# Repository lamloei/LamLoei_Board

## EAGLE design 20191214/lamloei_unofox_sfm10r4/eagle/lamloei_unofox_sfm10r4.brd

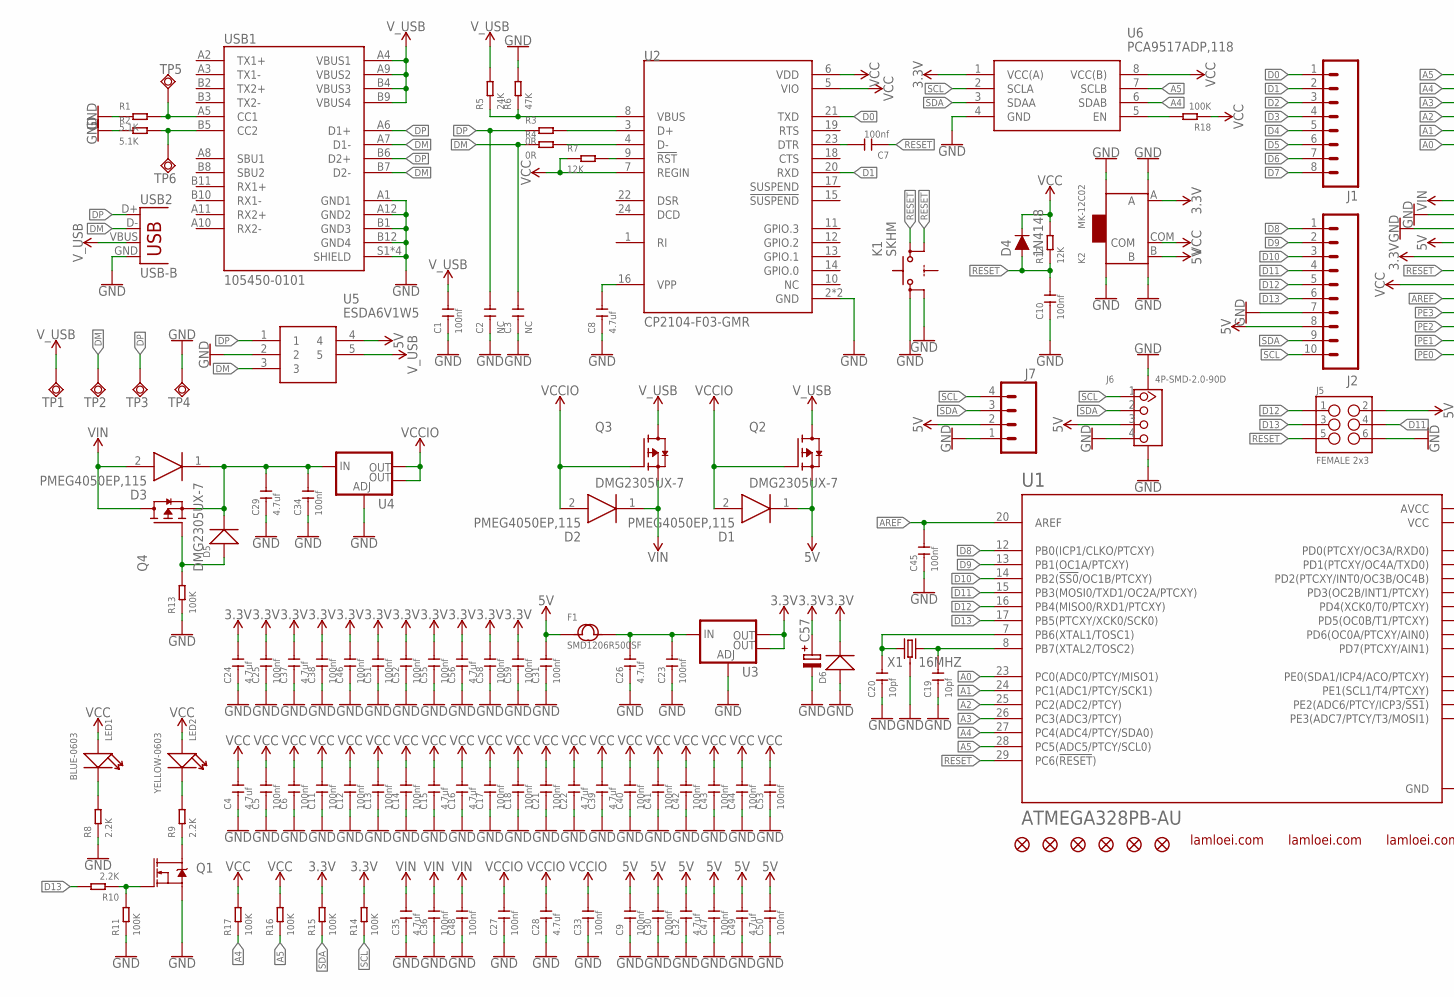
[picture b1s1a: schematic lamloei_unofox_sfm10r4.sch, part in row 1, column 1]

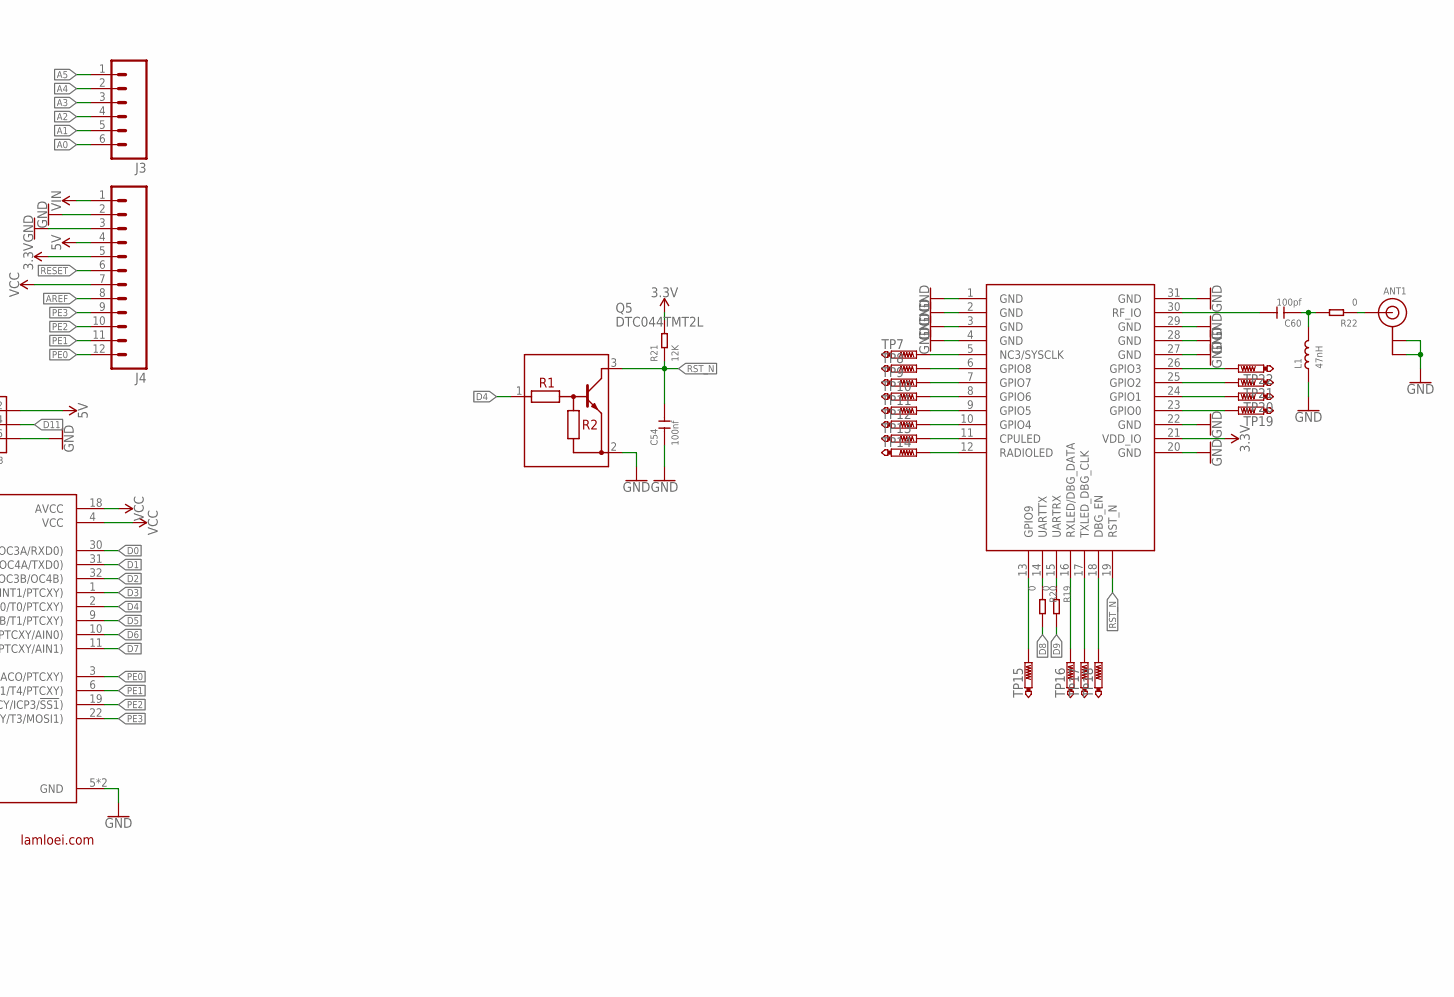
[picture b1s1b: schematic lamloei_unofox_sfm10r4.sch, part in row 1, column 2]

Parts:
ANT1: ANTENNA_U.FL; U.FL
C1, C5, C6, C7, C9, C10, C11, C12, C13, C14, C17, C18, C21, C23, C25, C27, C30, C31, C33, C34, C36, C38, C40, C41, C42, C43, C44, C45, C46, C47, C48, C50, C51, C52, C53, C54, C55, C58, C59: 100nf; C0402
C2, C3: NC; C0402
C4, C8, C15, C16, C22, C24, C26, C28, C29, C32, C35, C37, C39, C49, C56: 4.7uf; C0805
C19, C20: 10pf; C0402
C57: C-PR-SMD-TE-D; TE-D-7343
C60: 100pf; C0402
D1, D2, D3: PMEG4050EP,115; SODFL4725X110N
D4: 1N4148; SOD-323
D5, D6: DIODE'1N4148-SMD'; LL-34
F1: SMD1206R500SF; F1206
J1: M08SILK_FEMALE_PTH; 1X08
J2: M10SILK_FEMALE_PTH; 1X10
J3: M06SILK_FEMALE_PTH; 1X06
J4: M12PTH; 1X12
J5: FEMALE 2x3; 2X3
J6: 4P-SMD-2.0-90D; HW4-SMD-2.0-90D
J7: M04LONGPADS; 1X04_LONGPADS
K1: SKHM
K2: MK-12C02; SW7-SMD-L6.7X2.7X3.2MM
L1: 47nH; L0603
LED1: BLUE-0603; LED-0603
LED2: YELLOW-0603; LED-0603
Q1: 220mA/50V/3.5Ω; SOT23-3
Q2, Q3, Q4: DMG2305UX-7; SOT91P240X110-3N_DMG2305UX-7
Q5: DTC044TMT2L; SOTFL40P120X55-3N
R1, R2: 5.1K; R0402
R3, R4: 0R; R0402
R5: 24K; R0402
R6: 47K; R0402
R7, R12, R21: 12K; R0402
R8, R9, R10: 2.2K; R0402
R11, R13, R14, R15, R16, R17, R18: 100K; R0402
R19, R20, R22: 0; R0402
TP1, TP2, TP3, TP4, TP5, TP6: TPSQTP13SQ; TP13SQ
TP7, TP8, TP9, TP10, TP11, TP12, TP13, TP14, TP15, TP16, TP17, TP18, TP19, TP20, TP21, TP22: PTR1B1,27; B1,27
U1: ATMEGA328PB-AU; QFP80P900X900X120-32N
U2: CP2104-F03-GMR
U3, U4: V_REG_LM1117SOT223; SOT223
U5: ESDA6V1W5; SOT65P210X110-5N
U6: PCA9517ADP,118; SOP65P490X110-8N
U7: WSSFM10RWSSFM10R2R4; WSSFM10R
USB1: 105450-0101
USB2: USB-B; USB-B-PTH
X1: 16MHZ; CRYSTAL-SMD-3.2X2.5MM
ZFC1, ZFC2, ZFC3: FIDUCIAL1X2; FIDUCIAL-1X2
ZFD1, ZFD2, ZFD3: FIDUCIAL1X2; FIDUCIAL-1X2
ZL1, ZL2: LAMLEOI_LOGO_3
ZL3: LAMLOEI_BIGLOGO

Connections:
3.3V: C24.2, C25.2, C37.2, C38.2, C46.2, C51.2, C52.2, C55.2, C56.2, C57.+, C58.2, C59.2, D6.C (-), J4.5, K2.A, R14.2, R15.2, R21.2, U3.2 (OUT), U3.4 (OUT), U6.1 (VCC(A)), U7.21 (VDD_IO)
5V: C9.2, C30.2, C31.2, C32.2, C47.2, C49.2, C50.2, D1.1 (K), F1.1, J2.8, J4.4, J5.2, J6.3, J7.2, K2.B, Q2.2 (S), U5.4
A0: J3.6, U1.23 (PC0(ADC0/PTCY/MISO1))
A1: J3.5, U1.24 (PC1(ADC1/PTCY/SCK1))
A2: J3.4, U1.25 (PC2(ADC2/PTCY))
A3: J3.3, U1.26 (PC3(ADC3/PTCY))
A4: J3.2, R17.1, U1.27 (PC4(ADC4/PTCY/SDA0)), U6.6 (SDAB)
A5: J3.1, R16.1, U1.28 (PC5(ADC5/PTCY/SCL0)), U6.7 (SCLB)
AREF: C45.2, J4.8, U1.20 (AREF)
D0: J1.1, U1.30 (PD0(PTCXY/OC3A/RXD0)), U2.21 (TXD)
D1: J1.2, U1.31 (PD1(PTCXY/OC4A/TXD0)), U2.20 (RXD)
D2: J1.3, U1.32 (PD2(PTCXY/INT0/OC3B/OC4B))
D3: J1.4, U1.1 (PD3(OC2B/INT1/PTCXY))
D4: J1.5, Q5.1 (B), U1.2 (PD4(XCK0/T0/PTCXY))
D5: J1.6, U1.9 (PD5(OC0B/T1/PTCXY))
D6: J1.7, U1.10 (PD6(OC0A/PTCXY/AIN0))
D7: J1.8, U1.11 (PD7(PTCXY/AIN1))
D8: J2.1, R20.2, U1.12 (PB0(ICP1/CLKO/PTCXY))
D9: J2.2, R19.2, U1.13 (PB1(OC1A/PTCXY))
D10: J2.3, U1.14 (PB2(!SS0!/OC1B/PTCXY))
D11: J2.4, J5.4, U1.15 (PB3(MOSI0/TXD1/OC2A/PTCXY))
D12: J2.5, J5.1, U1.16 (PB4(MISO0/RXD1/PTCXY))
D13: J2.6, J5.3, R10.2, U1.17 (PB5(PTCXY/XCK0/SCK0))
DM: C3.2, R4.1, TP2.TP, U5.3, USB1.A7 (D1-), USB1.B7 (D2-), USB2.D-
DP: C2.2, R3.1, TP3.TP, U5.1, USB1.A6 (D1+), USB1.B6 (D2+), USB2.D+
GND: ANT1.1 (GND), ANT1.2 (GND), C1.1, C2.1, C3.1, C4.1, C5.1, C6.1, C8.1, C9.1, C10.1, C11.1, C12.1, C13.1, C14.1, C15.1, C16.1, C17.1, C18.1, C19.1, C20.1, C21.1, C22.1, C23.1, C24.1, C25.1, C26.1, C27.1, C28.1, C29.1, C30.1, C31.1, C32.1, C33.1, C34.1, C35.1, C36.1, C37.1, C38.1, C39.1, C40.1, C41.1, C42.1, C43.1, C44.1, C45.1, C46.1, C47.1, C48.1, C49.1, C50.1, C51.1, C52.1, C53.1, C54.1, C55.1, C56.1, C57.-, C58.1, C59.1, D6.A (+), J2.7, J4.2, J4.3, J5.6, J6.4, J6.SS1, J6.SS2, J7.1, K1.1, K1.2, K2.SS1, K2.SS2, K2.SS3, K2.SS4, L1.1, Q1.2 (S), Q5.2 (E), R1.1, R2.1, R6.2, R8.1, R11.1, R13.1, TP4.TP, U1.5 (GND), U1.21 (GND), U2.2 (GND), U2.25 (GND), U3.1 (ADJ), U4.1 (ADJ), U5.2, U6.4 (GND), U7.1 (GND), U7.2 (GND), U7.3 (GND), U7.4 (GND), U7.20 (GND), U7.22 (GND), U7.27 (GND), U7.28 (GND), U7.29 (GND), U7.31 (GND), USB1.A1 (GND1), USB1.A12 (GND2), USB1.B1 (GND3), USB1.B12 (GND4), USB1.S1 (SHIELD), USB1.S2 (SHIELD), USB1.S3 (SHIELD), USB1.S4 (SHIELD), USB2.GND, X1.2 (3), X1.4 (3)
unnamed: R2.2, TP6.TP, USB1.B5 (CC2)
unnamed: R1.2, TP5.TP, USB1.A5 (CC1)
unnamed: R3.2, U2.3 (D+)
unnamed: R4.2, U2.4 (D-)
unnamed: R5.1, R6.1, U2.8 (VBUS)
unnamed: C23.2, C26.2, F1.2, U3.3 (IN)
unnamed: LED1.-, R8.2
unnamed: C20.2, U1.7 (PB6(XTAL1/TOSC1)), X1.1
unnamed: C7.2, U2.23 (DTR)
unnamed: C29.2, C34.2, D3.1 (K), D5.C (-), Q4.2 (S), U4.3 (IN)
unnamed: R7.2, U2.9 (!RST)
unnamed: LED2.-, R9.2
unnamed: C8.2, U2.16 (VPP)
unnamed: C60.2, U7.30 (RF_IO)
unnamed: C19.2, U1.8 (PB7(XTAL2/TOSC2)), X1.3 (2)
unnamed: R18.2, U6.5 (EN)
unnamed: C60.1, L1.2, R22.2
unnamed: Q1.1 (G), R10.1, R11.2
unnamed: Q1.3 (D), R9.1
unnamed: ANT1.3 (SIGNAL), R22.1
unnamed: R20.1, U7.14 (UARTTX)
unnamed: R19.1, U7.15 (UARTRX)
unnamed: D5.A (+), Q4.1 (G), R13.2
unnamed: TP7.TP, U7.5 (NC3/SYSCLK)
unnamed: TP8.TP, U7.6 (GPIO8)
unnamed: TP9.TP, U7.7 (GPIO7)
unnamed: TP10.TP, U7.8 (GPIO6)
unnamed: TP11.TP, U7.9 (GPIO5)
unnamed: TP12.TP, U7.10 (GPIO4)
unnamed: TP13.TP, U7.11 (CPULED)
unnamed: TP14.TP, U7.12 (RADIOLED)
unnamed: TP22.TP, U7.26 (GPIO3)
unnamed: TP21.TP, U7.25 (GPIO2)
unnamed: TP20.TP, U7.24 (GPIO1)
unnamed: TP19.TP, U7.23 (GPIO0)
unnamed: TP15.TP, U7.13 (GPIO9)
unnamed: TP18.TP, U7.18 (DBG_EN)
unnamed: TP17.TP, U7.17 (TXLED_DBG_CLK)
unnamed: TP16.TP, U7.16 (RXLED/DBG_DATA)
PE0: J4.12, U1.3 (PE0(SDA1/ICP4/ACO/PTCXY))
PE1: J4.11, U1.6 (PE1(SCL1/T4/PTCXY))
PE2: J4.10, U1.19 (PE2(ADC6/PTCY/ICP3/!SS1!))
PE3: J4.9, U1.22 (PE3(ADC7/PTCY/T3/MOSI1))
RESET: C7.1, C10.2, D4.A, J4.6, J5.5, K1.3 (S1), K1.4 (S2), R12.1, U1.29 (PC6(!RESET!))
RST_N: C54.2, Q5.3 (C), R21.1, U7.19 (RST_N)
SCL: J2.10, J6.1, J7.4, R14.1, U6.2 (SCLA)
SDA: J2.9, J6.2, J7.3, R15.1, U6.3 (SDAA)
VCC: C4.2, C5.2, C6.2, C11.2, C12.2, C13.2, C14.2, C15.2, C16.2, C17.2, C18.2, C21.2, C22.2, C39.2, C40.2, C41.2, C42.2, C43.2, C44.2, C53.2, D4.C, J4.7, K2.COM, LED1.+, LED2.+, R7.1, R12.2, R16.2, R17.2, R18.1, U1.4 (VCC), U1.18 (AVCC), U2.5 (VIO), U2.6 (VDD), U2.7 (REGIN), U6.8 (VCC(B))
VCCIO: C27.2, C28.2, C33.2, D1.2 (A), D2.2 (A), Q2.1 (G), Q3.1 (G), U4.2 (OUT), U4.4 (OUT)
VIN: C35.2, C36.2, C48.2, D2.1 (K), D3.2 (A), J4.1, Q3.2 (S), Q4.3 (D)
V_USB: C1.2, Q2.3 (D), Q3.3 (D), R5.2, TP1.TP, U5.5, USB1.A4 (VBUS1), USB1.A9 (VBUS2), USB1.B4 (VBUS3), USB1.B9 (VBUS4), USB2.VBUS

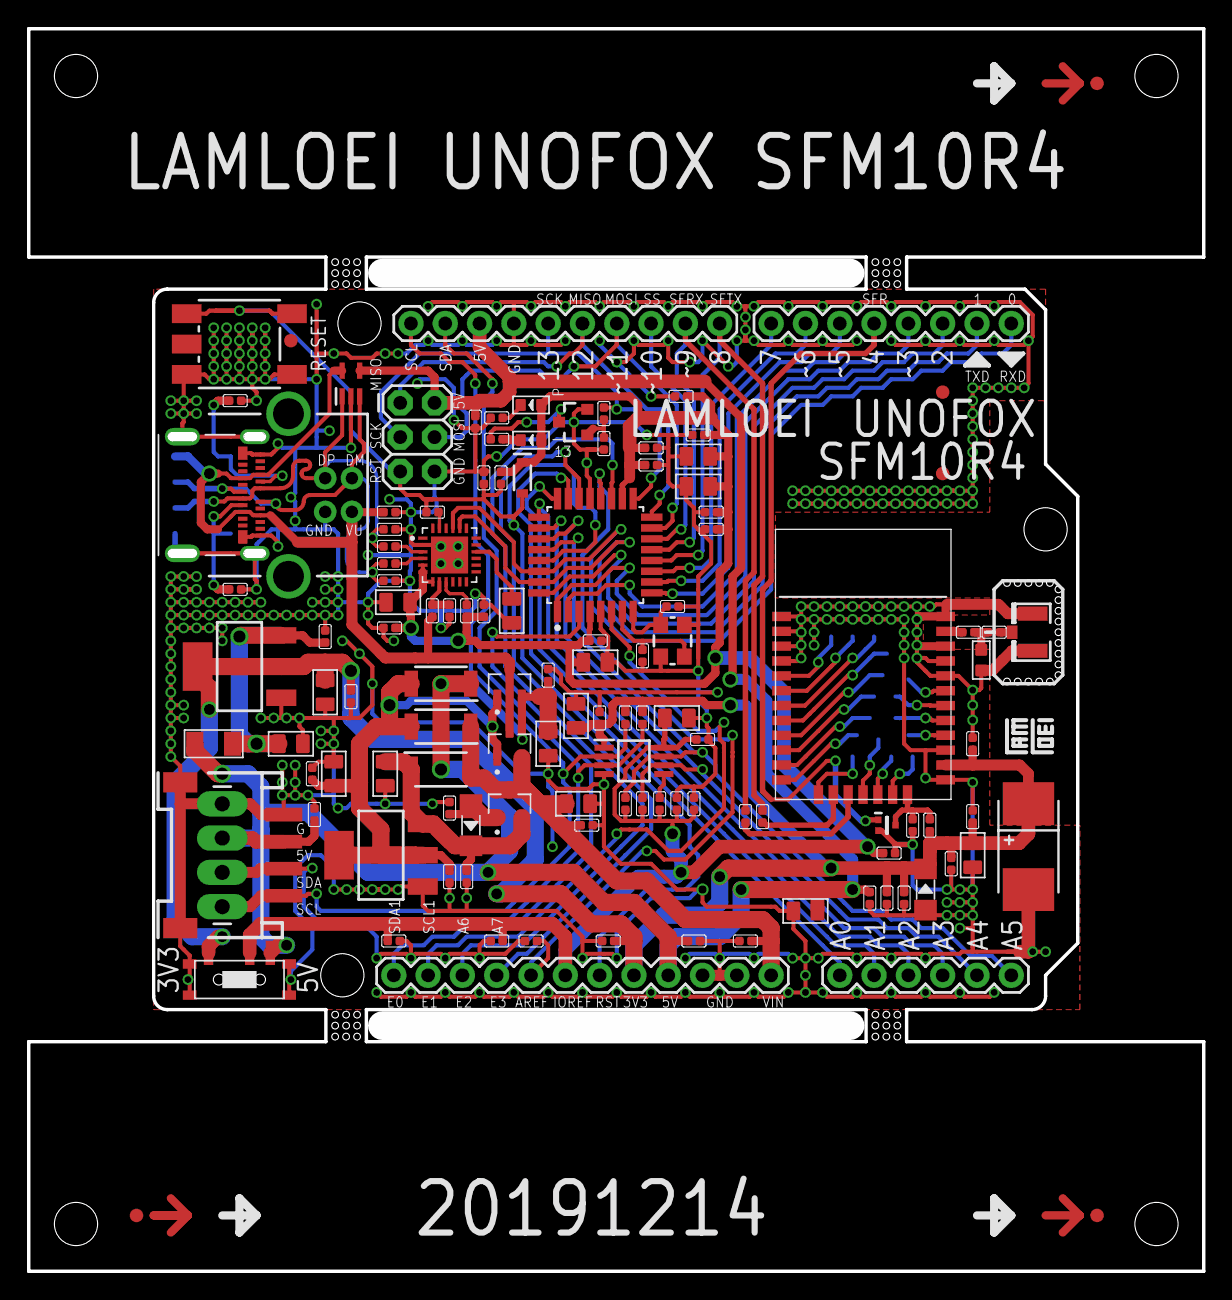
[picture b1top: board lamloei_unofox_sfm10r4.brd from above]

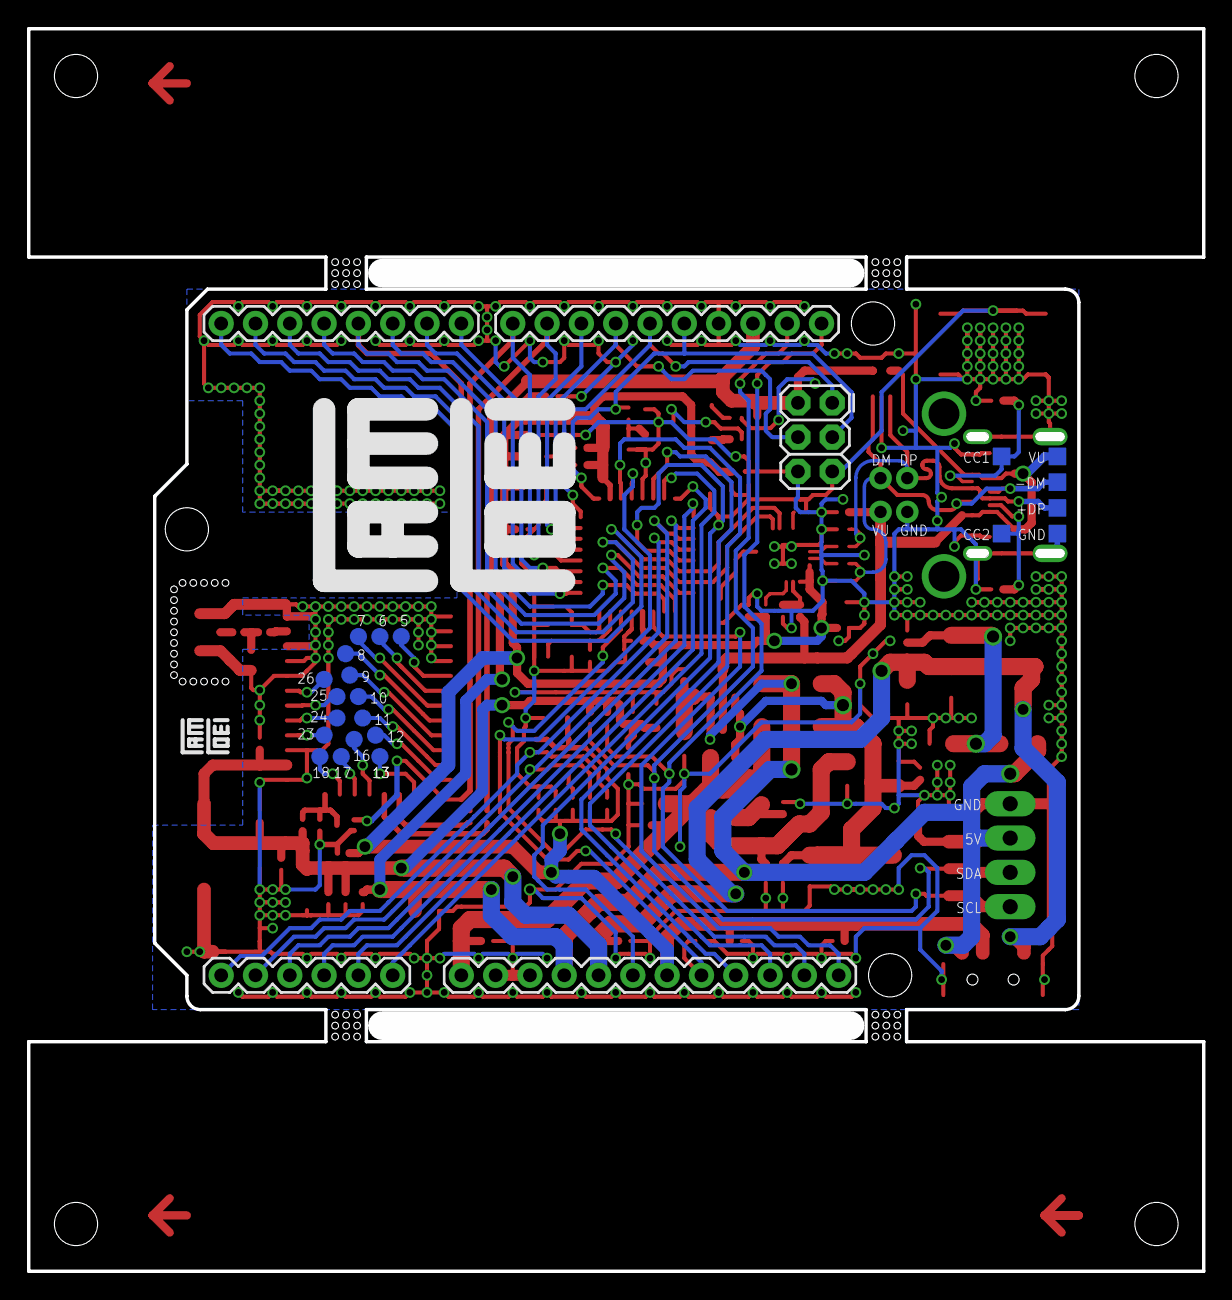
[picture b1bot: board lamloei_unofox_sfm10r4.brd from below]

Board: 2 copper layers, 87.0 x 92.0 mm, 148 parts (24 on the bottom side), 77 nets.

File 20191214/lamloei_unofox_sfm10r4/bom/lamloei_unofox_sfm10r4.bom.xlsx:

|  | LamLoei UNOFOX SFM10R4 |  | v1 | 43813
Item | Quantity | Reference | Part | Footprint | Mfg | Mfg P/N | Vendor | Vendor P/N | Notes
1 | 1 | ANT1 | RF Connectors/Coaxial Connectors | U.FL | Hirose | U.FL-R-SMT-1(10) | LCSC | C88373
2 | 39 | C1, C5, C6, C7, C9, C10, C11, C12, C13, C14, C17, C18, C21, C23, C25, C27, C30,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 | CAP CER 100nF ±10% 50V X7R | 0402 | Murata | GRM155R71H104KE14D | LCSC | C77020
3 | 2 | C2, C3 | NC | 0402 |  |  |  |  | Not installed
4 | 15 | C4, C8, C15, C16, C22, C24, C26, C28, C29, C32, C35, C37, C39, C49, C56 | CAP CER 4.7uF ±10% 25V X7R | 0805 | Murata | GRM21BR71E475KA73L | LCSC | C162427
5 | 2 | C19, C20 | CAP CER 10pF ±5% 50V C0G | 0402 | Murata | GRM1555C1H100JA01D | LCSC | C76946
6 | 1 | C57 | CAP TAN 470uF ±20% 6.3V | 7343 | PANASONIC | 6TPE470MAZU | LCSC | C79114
7 | 1 | C60 | CAP CER 100pF ±2% 50V C0G | 0402 | Murata | GRM1555C1H101GA01D | LCSC | C161522
8 | 3 | D1, D2, D3 | Schottky Barrier Diodes (SBD) 40V 5A | SOD-128 | Nexperia | PMEG4050EP,115 | LCSC | C96235
9 | 1 | D4 | Switching Diode 75V 150mA 1.25V | SOD-323 | Diodes | 1N4148WS-7-F | LCSC | C60580
10 | 1 | D5 | Zener Diodes 12V 500mW | LL-34 | ST(Semtech) | ZMM12 | LCSC | C7172
11 | 1 | D6 | Zener Diodes 3.6V 500mW | LL-34 | ST(Semtech) | ZMM3V6 | LCSC | C8057
12 | 1 | F1 | PTC Resettable Fuses 6V 1.5A | 1206 | BOURNS | MF-NSMF075-2 | LCSC | C89653
13 | 1 | J1 | Female Header 8 1 P=2.54mm | 8-PTH | CJT | A2541HWV-8P | LCSC | C225505
14 | 1 | J2 | Female Header 10 1 P=2.54mm | 10-PTH | CJT | A2541HWV-10P | LCSC | C225507
15 | 1 | J3 | Female Header 6 1 P=2.54mm | 6-PTH | CJT | A2541HWV-6P | LCSC | C225503
16 | 1 | J4 | Female Header 12 1 P=2.54mm | 12-PTH | CJT | A2541HWV-12P | LCSC | C225509
17 | 1 | J5 | Female Header 6 2 P=2.54mm | 6-PTH | CJT | A2541WV-2x3P | LCSC | C225518
18 | 1 | J6 | HY Header Male Pin 0.079"(2.00mm) | 4-SMD | BOOMELE | C146060 | LCSC | C146060
19 | 1 | J7 | NC | 4-PTH |  |  |  |  | Not installed
20 | 1 | K1 | SPST-NO 50mA @ 12VDC | 5-SMD | ALPS | SKHMQME010 | LCSC | C115345
21 | 1 | K2 | SPST-NO 50mA @ 12VDC | 2-SMD | ALPS | SKRKAEE020 | LCSC | C115357
22 | 1 | L1 | Inductors 47nH ±2% 380mA 290mΩ | 0603 | Murata | LQW18AN47NG00D | LCSC | C98076
23 | 1 | LED1 | Light Emitting Diodes (LED) Blue 465~475nm | 0603 | Everlight | 19-217/BHC-ZL1M2RY/3T | LCSC | C72041
24 | 1 | LED2 | Light Emitting Diodes (LED) Yellow 585.5~591.5nm | 0603 | Everlight | 19-213/Y2C-CQ2R2L/3T(CY) | LCSC | C72038
25 | 1 | Q1 | N Channel 60V 115mA | SOT-23-3 | Diodes | 2N7002-7-F | LCSC | C85049
26 | 3 | Q2, Q3, Q4 | MOSFET P Channel 20V 4.2A | SOT-23-3 | Diodes | DMG2305UX-7 | LCSC | C150470
27 | 1 | Q5 | Digital Transistors NPN - Pre-Biased 100mA 50V | SOT-723 | ROHM | DTC043ZMT2L | LCSC | C308683
28 | 2 | R1, R2 | RES SMD 5.1K OHM 1% 1/16W | 0402 | Yageo | RC0402FR-075K1L | LCSC | C105872
29 | 5 | R3, R4, R19, R20, R22 | RES SMD 0 OHM 1% 1/16W | 0402 | Yageo | RC0402FR-070RL | LCSC | C106231
30 | 1 | R5 | RES SMD 24K OHM 1% 1/16W | 0402 | Yageo | RC0402FR-0724KL | LCSC | C138026
31 | 1 | R6 | RES SMD 47K OHM 1% 1/16W | 0402 | Yageo | RC0402FR-0747KL | LCSC | C93943
32 | 3 | R7, R12, R21 | RES SMD 12K OHM 1% 1/16W | 0402 | Yageo | RC0402FR-0712KL | LCSC | C114760
33 | 3 | R8, R9, R10 | RES SMD 2.2K OHM 1% 1/16W | 0402 | Yageo | RC0402FR-072K2L | LCSC | C114762
34 | 7 | R11, R13, R14, R15, R16, R17, R18 | RES SMD 100K OHM 1% 1/16W | 0402 | Yageo | RC0402FR-07100KL | LCSC | C60491
35 | 1 | U1 | 8-Bit FLASH AVR 20MHz | TQFP-32_7x7x08P | Microchip | ATMEGA328PB-AU | LCSC | C132230
36 | 1 | U2 | Transceiver USB 1/1 2Mbps | QFN-24 | SILICON LABS | CP2104-F03-GMR | LCSC | C47742
37 | 1 | U3 | Fixed 15V 3.3V 800mA | SOT-223 | Texas | LM1117MPX-3.3/NOPB | LCSC | C9662
38 | 1 | U4 | Fixed 15V 5V 800mA | SOT-223 | Texas | LM1117MPX-5.0/NOPB | LCSC | C9663
39 | 1 | U5 | Unidirectional 3V 6.1V | SOT-323-5 | STMicro | ESDA6V1W5 | LCSC | C48677
40 | 1 | U6 | Buffers | TSSOP-8_3x3x065P | NXP | PCA9517ADP,118 | LCSC | C80799
41 | 1 | U7 | Wisol Sigfox Module WSSFM10R4AT | 31-SMD | WISOL | WSSFM10R4AT | glynstore |  | https://www.glynstore.com/wisol-sigfox-module-wssfm10r4at/
42 | 1 | USB1 | USB - Type C Receptacle | 24-SMD | MOLEX | 105450-0101 | LCSC | C134092
43 | 1 | USB2 | NC - USB - Type B Receptacle USB 2 4 | 4-PTH | MOLEX | 67068-8000 | LCSC | C114097 | Not installed
44 | 1 | X1 | SMD Crystal 16MHz ±20ppm 10pF 80Ω | SMD-3225_4P | Seiko Epson | X1E0003410273 | LCSC | C255906

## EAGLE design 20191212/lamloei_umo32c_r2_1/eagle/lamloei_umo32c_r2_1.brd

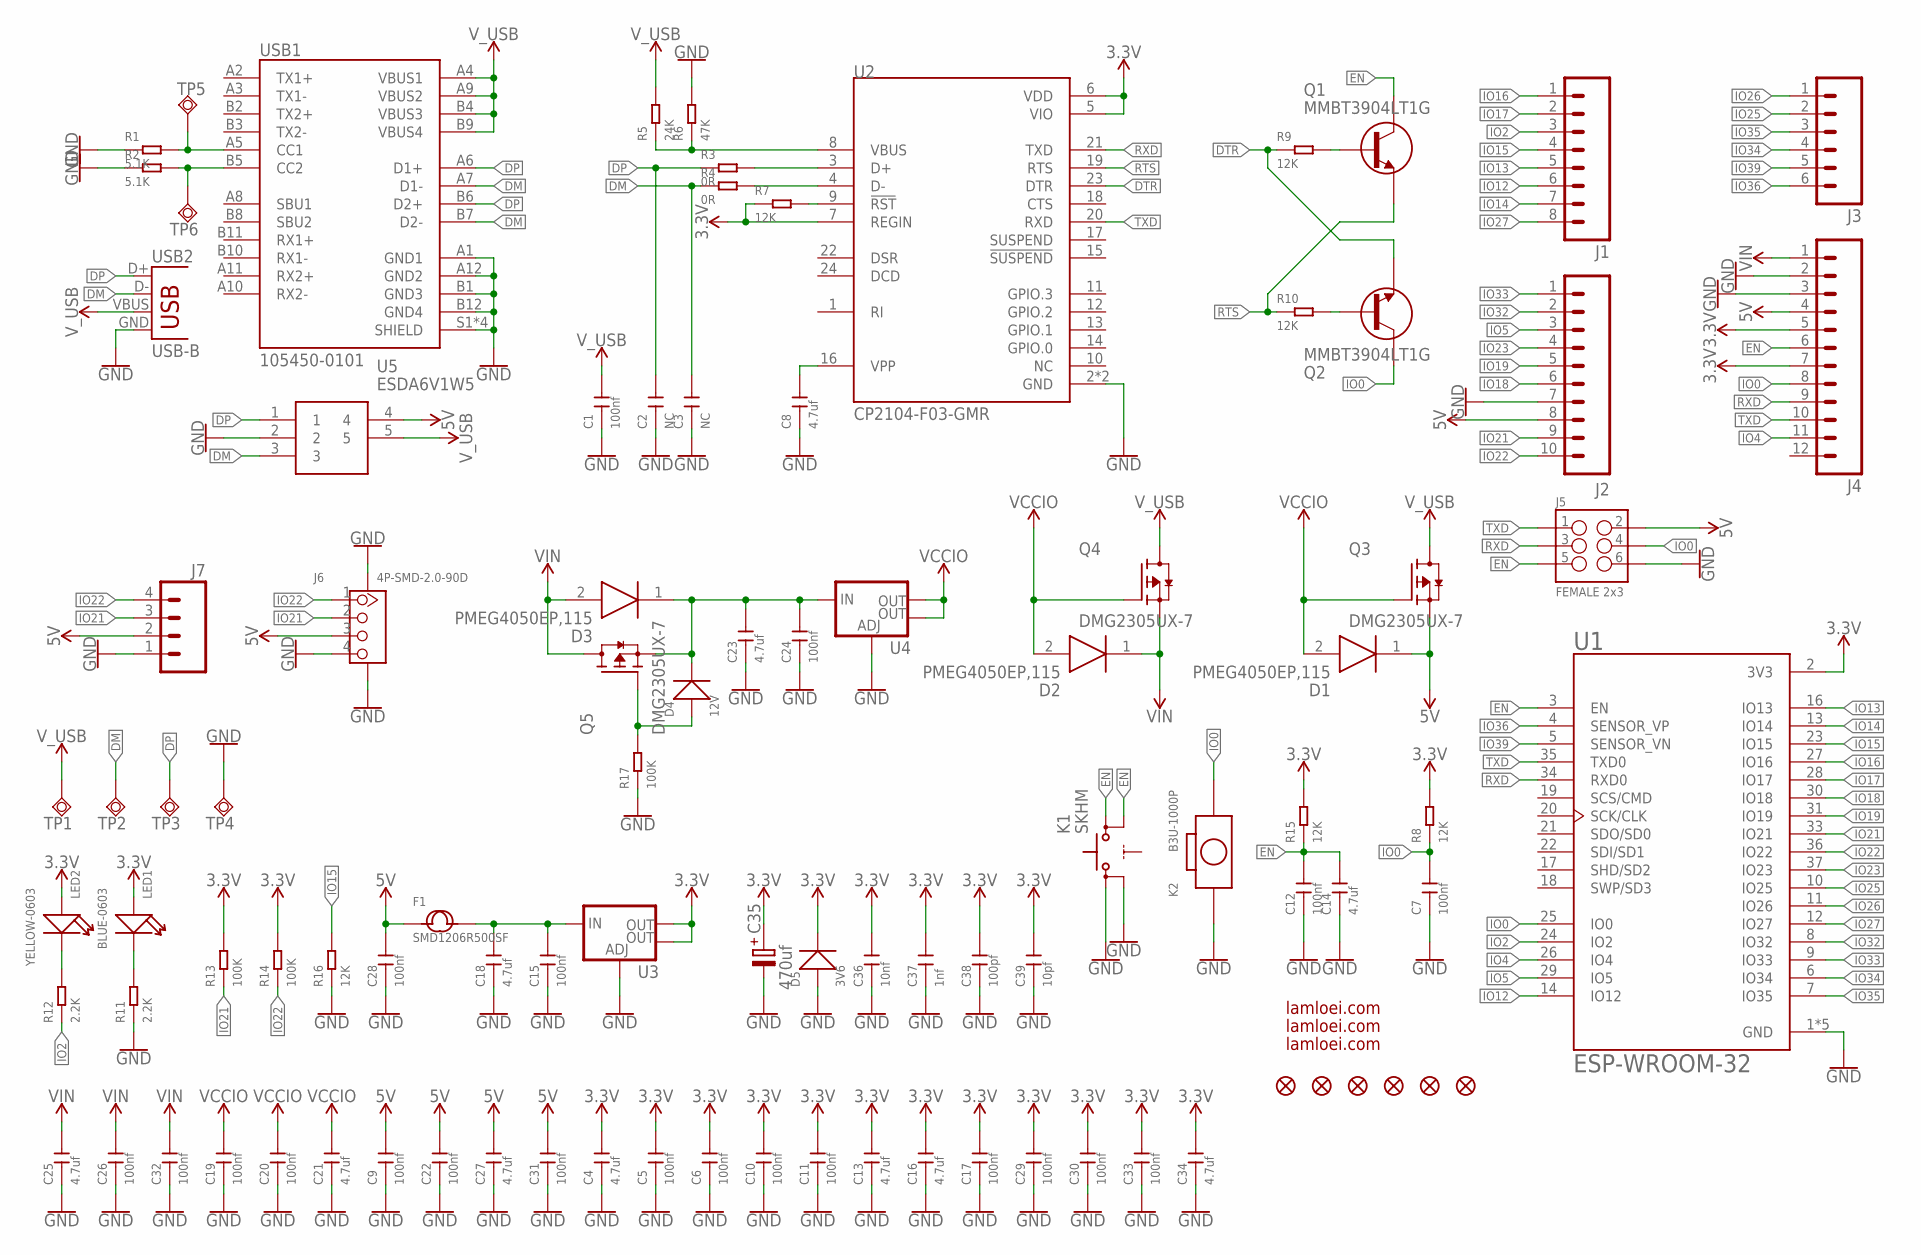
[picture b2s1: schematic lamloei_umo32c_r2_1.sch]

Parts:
C1, C5, C6, C7, C9, C10, C11, C12, C15, C17, C19, C20, C22, C24, C26, C28, C29, C30, C31, C32, C33: 100nf; C0402
C2, C3: NC; C0402
C4, C8, C13, C14, C16, C18, C21, C23, C25, C27, C34: 4.7uf; C0805
C35: 470uf; TE-D-7343
C36: 10nf; C0402
C37: 1nf; C0402
C38: 100pf; C0402
C39: 10pf; C0402
D1, D2, D3: PMEG4050EP,115; SODFL4725X110N
D4: 12V; LL-34
D5: 3V6; LL-34
F1: SMD1206R500SF; F1206
J1: M08SILK_FEMALE_PTH; 1X08
J2: M10SILK_FEMALE_PTH; 1X10
J3: M06SILK_FEMALE_PTH; 1X06
J4: M12PTH; 1X12
J5: FEMALE 2x3; 2X3
J6: 4P-SMD-2.0-90D; HW4-SMD-2.0-90D
J7: M04LONGPADS; 1X04_LONGPADS
K1: SKHM
K2: B3U-1000P; SW2-SMD-3.0X2.5X1.2+0.4MM
LED1: BLUE-0603; LED-0603
LED2: YELLOW-0603; LED-0603
Q1, Q2: MMBT3904LT1G; SOT23
Q3, Q4, Q5: DMG2305UX-7; SOT91P240X110-3N_DMG2305UX-7
R1, R2: 5.1K; R0402
R3, R4: 0R; R0402
R5: 24K; R0402
R6: 47K; R0402
R7, R8, R9, R10, R15, R16: 12K; R0402
R11, R12: 2.2K; R0402
R13, R14, R17: 100K; R0402
TP1, TP2, TP3, TP4, TP5, TP6: TPSQTP13SQ; TP13SQ
U1: ESP-WROOM-32; MODULE_ESP-WROOM-32
U2: CP2104-F03-GMR
U3, U4: V_REG_LM1117SOT223; SOT223
U5: ESDA6V1W5; SOT65P210X110-5N
USB1: 105450-0101
USB2: USB-B; USB-B-PTH
ZFC1, ZFC2, ZFC3: FIDUCIAL1X2; FIDUCIAL-1X2
ZFD1, ZFD2, ZFD3: FIDUCIAL1X2; FIDUCIAL-1X2
ZL1, ZL2: LAMLEOI_LOGO_3
ZL3: LAMLOEI_BIGLOGO

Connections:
3.3V: C4.2, C5.2, C6.2, C10.2, C11.2, C13.2, C16.2, C17.2, C29.2, C30.2, C33.2, C34.2, C35.+, C36.2, C37.2, C38.2, C39.2, D5.C (-), J4.5, J4.7, LED1.+, LED2.+, R7.1, R8.2, R13.2, R14.2, R15.2, U1.2 (3V3), U2.5 (VIO), U2.6 (VDD), U2.7 (REGIN), U3.2 (OUT), U3.4 (OUT)
5V: C9.2, C22.2, C27.2, C28.2, C31.2, D1.1 (K), F1.1, J2.8, J4.4, J5.2, J6.3, J7.2, Q3.2 (S), U5.4
DM: C3.2, R4.1, TP2.TP, U5.3, USB1.A7 (D1-), USB1.B7 (D2-), USB2.D-
DP: C2.2, R3.1, TP3.TP, U5.1, USB1.A6 (D1+), USB1.B6 (D2+), USB2.D+
DTR: Q2.2 (E), R9.1, U2.23 (DTR)
EN: C12.2, C14.2, J4.6, J5.5, K1.3 (S1), K1.4 (S2), Q1.3 (C), R15.1, U1.3 (EN)
GND: C1.1, C2.1, C3.1, C4.1, C5.1, C6.1, C7.1, C8.1, C9.1, C10.1, C11.1, C12.1, C13.1, C14.1, C15.1, C16.1, C17.1, C18.1, C19.1, C20.1, C21.1, C22.1, C23.1, C24.1, C25.1, C26.1, C27.1, C28.1, C29.1, C30.1, C31.1, C32.1, C33.1, C34.1, C35.-, C36.1, C37.1, C38.1, C39.1, D5.A (+), J2.7, J4.2, J4.3, J5.6, J6.4, J6.SS1, J6.SS2, J7.1, K1.1, K1.2, K2.1, R1.1, R2.1, R6.2, R11.1, R16.1, R17.1, TP4.TP, U1.1 (GND), U1.1.1 (GND), U1.1.2 (GND), U1.15 (GND), U1.38 (GND), U2.2 (GND), U2.25 (GND), U3.1 (ADJ), U4.1 (ADJ), U5.2, USB1.A1 (GND1), USB1.A12 (GND2), USB1.B1 (GND3), USB1.B12 (GND4), USB1.S1 (SHIELD), USB1.S2 (SHIELD), USB1.S3 (SHIELD), USB1.S4 (SHIELD), USB2.GND
IO0: C7.2, J4.8, J5.4, K2.2, Q2.3 (C), R8.1, U1.25 (IO0)
IO2: J1.3, R12.1, U1.24 (IO2)
IO4: J4.11, U1.26 (IO4)
IO5: J2.3, U1.29 (IO5)
IO12: J1.6, U1.14 (IO12)
IO13: J1.5, U1.16 (IO13)
IO14: J1.7, U1.13 (IO14)
IO15: J1.4, R16.2, U1.23 (IO15)
IO16: J1.1, U1.27 (IO16)
IO17: J1.2, U1.28 (IO17)
IO18: J2.6, U1.30 (IO18)
IO19: J2.5, U1.31 (IO19)
IO21: J2.9, J6.2, J7.3, R13.1, U1.33 (IO21)
IO22: J2.10, J6.1, J7.4, R14.1, U1.36 (IO22)
IO23: J2.4, U1.37 (IO23)
IO25: J3.2, U1.10 (IO25)
IO26: J3.1, U1.11 (IO26)
IO27: J1.8, U1.12 (IO27)
IO32: J2.2, U1.8 (IO32)
IO33: J2.1, U1.9 (IO33)
IO34: J3.4, U1.6 (IO34)
IO35: J3.3, U1.7 (IO35)
IO36: J3.6, U1.4 (SENSOR_VP)
IO39: J3.5, U1.5 (SENSOR_VN)
unnamed: R2.2, TP6.TP, USB1.B5 (CC2)
unnamed: R1.2, TP5.TP, USB1.A5 (CC1)
unnamed: R3.2, U2.3 (D+)
unnamed: R4.2, U2.4 (D-)
unnamed: R5.1, R6.1, U2.8 (VBUS)
unnamed: C15.2, C18.2, F1.2, U3.3 (IN)
unnamed: LED1.-, R11.2
unnamed: Q1.1 (B), R9.2
unnamed: Q2.1 (B), R10.2
unnamed: C23.2, C24.2, D3.1 (K), D4.C (-), Q5.2 (S), U4.3 (IN)
unnamed: R7.2, U2.9 (!RST)
unnamed: LED2.-, R12.2
unnamed: C8.2, U2.16 (VPP)
unnamed: D4.A (+), Q5.1 (G), R17.2
RTS: Q1.2 (E), R10.1, U2.19 (RTS)
RXD: J4.9, J5.3, U1.34 (RXD0), U2.21 (TXD)
TXD: J4.10, J5.1, U1.35 (TXD0), U2.20 (RXD)
VCCIO: C19.2, C20.2, C21.2, D1.2 (A), D2.2 (A), Q3.1 (G), Q4.1 (G), U4.2 (OUT), U4.4 (OUT)
VIN: C25.2, C26.2, C32.2, D2.1 (K), D3.2 (A), J4.1, Q4.2 (S), Q5.3 (D)
V_USB: C1.2, Q3.3 (D), Q4.3 (D), R5.2, TP1.TP, U5.5, USB1.A4 (VBUS1), USB1.A9 (VBUS2), USB1.B4 (VBUS3), USB1.B9 (VBUS4), USB2.VBUS

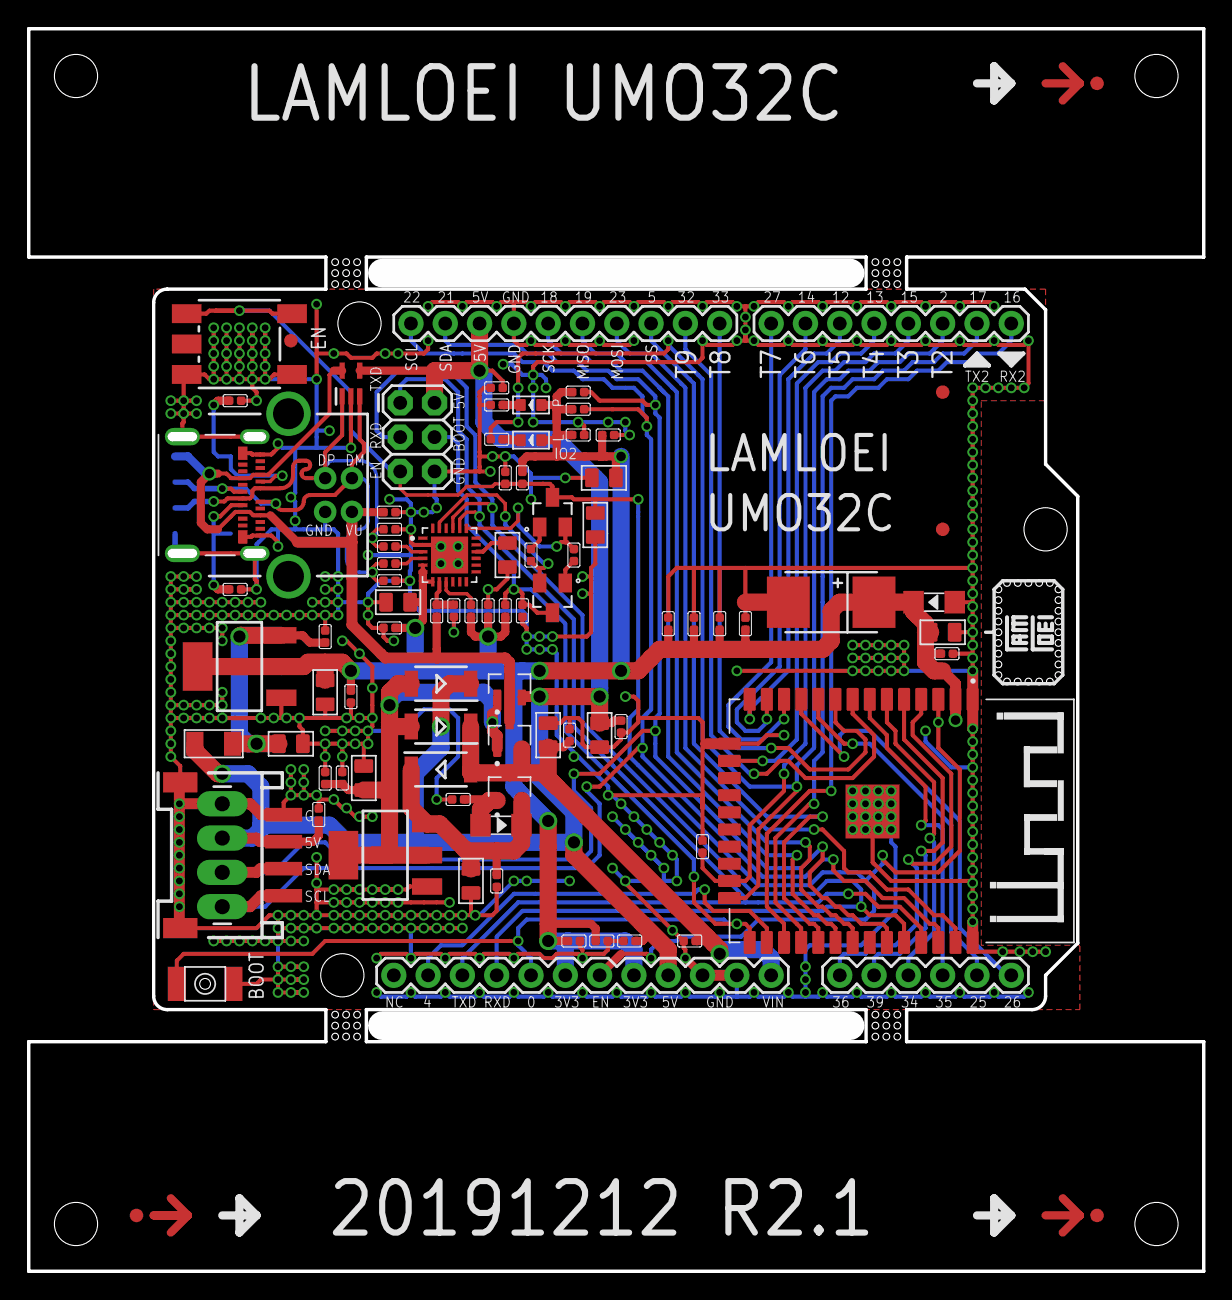
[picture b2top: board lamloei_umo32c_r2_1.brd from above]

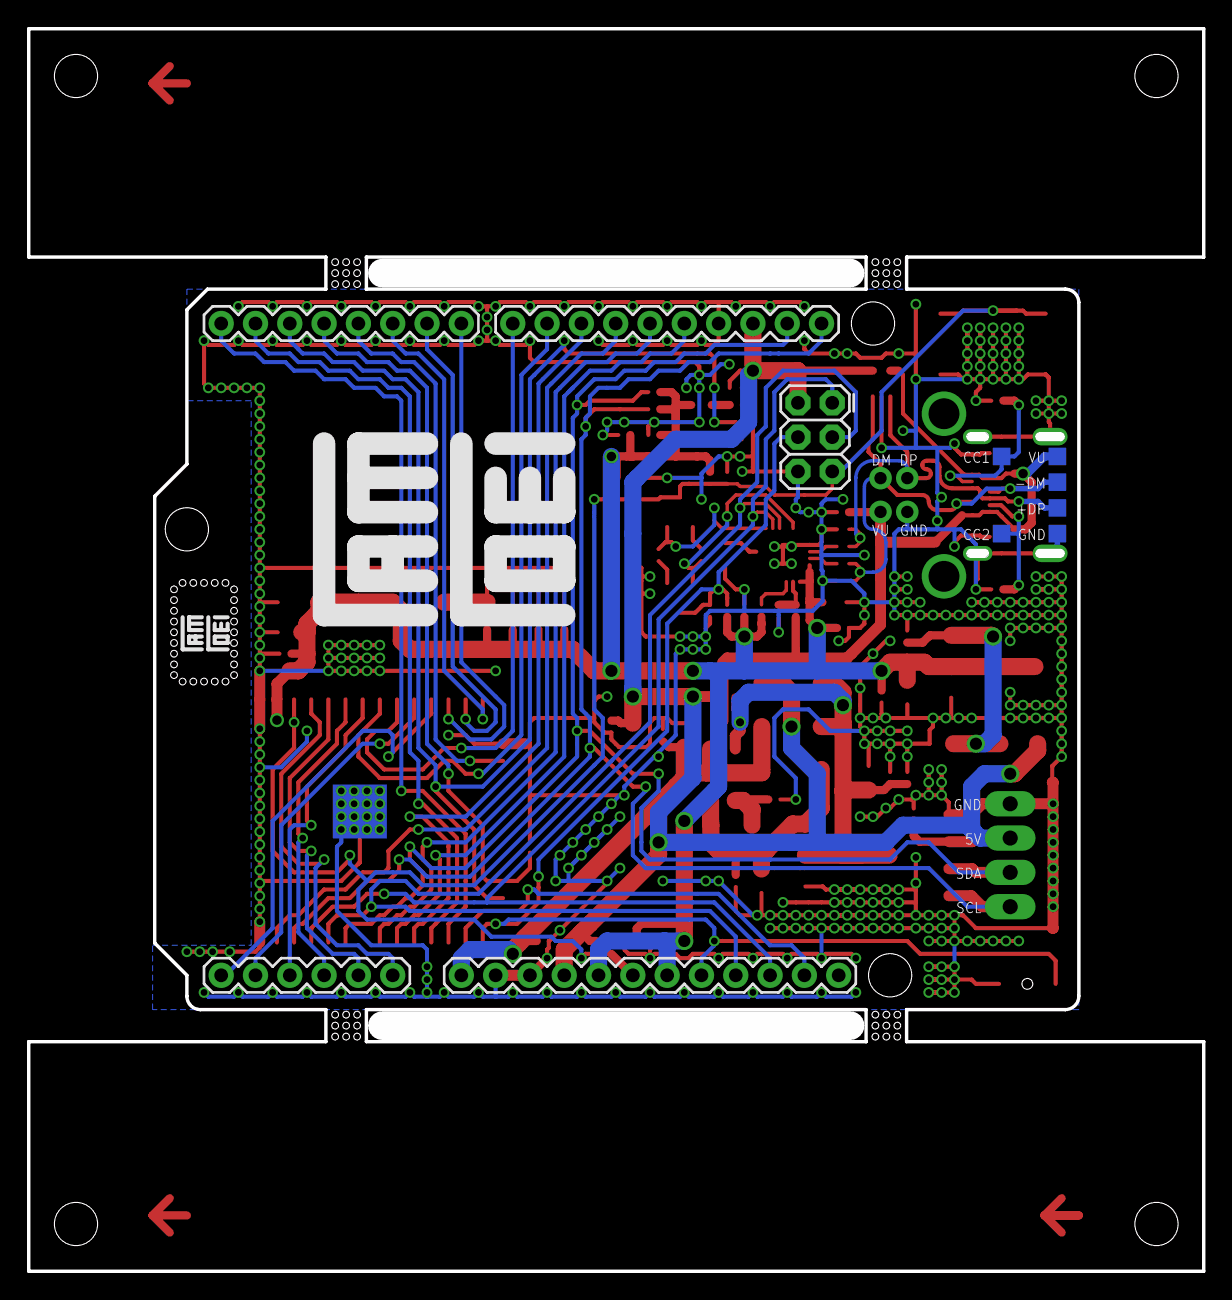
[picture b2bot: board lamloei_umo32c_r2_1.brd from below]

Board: 2 copper layers, 87.0 x 92.0 mm, 100 parts (8 on the bottom side), 51 nets.

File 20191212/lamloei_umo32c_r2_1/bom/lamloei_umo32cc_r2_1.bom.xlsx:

|  | LamLoei UMO32C |  | v2.1 | 43811
Item | Quantity | Reference | Part | Footprint | Mfg | Mfg P/N | Vendor | Vendor P/N | Notes
1 | 21 | C1, C5, C6, C7, C9, C10, C11, C12, C15, C17, C19, C20, C22, C24, C26, C28, C29,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 | CAP CER 100nF ±10% 50V X7R | 0402 | Murata | GRM155R71H104KE14D | LCSC | C77020
2 | 2 | C2, C3 | NC | 0402 |  |  |  |  | Not installed
3 | 11 | C4, C8, C13, C14, C16, C18, C21, C23, C25, C27, C34 | CAP CER 4.7uF ±10% 25V X7R | 0805 | Murata | GRM21BR71E475KA73L | LCSC | C162427
4 | 1 | C35 | CAP TAN 470uF ±20% 6.3V | 7343 | PANASONIC | 6TPE470MAZU | LCSC | C79114
5 | 1 | C36 | CAP CER 10nF ±10% 25V X7R | 0402 | Murata | GRM155R71E103KA01D | LCSC | C77013
6 | 1 | C37 | CAP CER 1nF ±10% 50V X7R | 0402 | Murata | GRM155R71H102JA01D | LCSC | C397298
7 | 1 | C38 | CAP CER 470pF ±5% 50V X7R | 0402 | Murata | GRM155R71H471JA01D | LCSC | C415539
8 | 1 | C39 | CAP CER 220pF ±10% 50V X7R | 0402 | Murata | GRM155R71H221KA01D | LCSC | C97872
9 | 3 | D1, D2, D3 | Schottky Barrier Diodes (SBD) 40V 5A | SOD-128 | Nexperia | PMEG4050EP,115 | LCSC | C96235
10 | 1 | D4 | Zener Diodes 12V 500mW | LL-34 | ST(Semtech) | ZMM12 | LCSC | C7172
11 | 1 | D5 | Zener Diodes 3.6V 500mW | LL-34 | ST(Semtech) | ZMM3V6 | LCSC | C8057
12 | 1 | F1 | PTC Resettable Fuses 6V 1.5A | 1206 | BOURNS | MF-NSMF075-2 | LCSC | C89653
13 | 1 | J1 | Female Header 8 1 P=2.54mm | 8-PTH | CJT | A2541HWV-8P | LCSC | C225505
14 | 1 | J2 | Female Header 10 1 P=2.54mm | 10-PTH | CJT | A2541HWV-10P | LCSC | C225507
15 | 1 | J3 | Female Header 6 1 P=2.54mm | 6-PTH | CJT | A2541HWV-6P | LCSC | C225503
16 | 1 | J4 | Female Header 12 1 P=2.54mm | 12-PTH | CJT | A2541HWV-12P | LCSC | C225509
17 | 1 | J5 | Female Header 6 2 P=2.54mm | 6-PTH | CJT | A2541WV-2x3P | LCSC | C225518
18 | 1 | J6 | HY Header Male Pin 0.079"(2.00mm) | 4-SMD | BOOMELE | C146060 | LCSC | C146060
19 | 1 | J7 | NC | 4-PTH |  |  |  |  | Not installed
20 | 1 | K1 | SPST-NO 50mA @ 12VDC | 5-SMD | ALPS | SKHMQME010 | LCSC | C115345
21 | 1 | K2 | SPST-NO 50mA @ 12VDC | 2-SMD | ALPS | SKRKAEE020 | LCSC | C115357
22 | 1 | LED1 | Light Emitting Diodes (LED) Blue 465~475nm | 0603 | Everlight | 19-217/BHC-ZL1M2RY/3T | LCSC | C72041
23 | 1 | LED2 | Light Emitting Diodes (LED) Yellow 585.5~591.5nm | 0603 | Everlight | 19-213/Y2C-CQ2R2L/3T(CY) | LCSC | C72038
24 | 2 | Q1, Q2 | NPN 100mA 45V 250mW | SOT-23-3 | Nexperia | BC847B,215 | LCSC | C57668
25 | 3 | Q3, Q4, Q5 | MOSFET P Channel 20V 4.2A | SOT-23-3 | Diodes | DMG2305UX-7 | LCSC | C150470
26 | 2 | R1, R2 | RES SMD 5.1K OHM 1% 1/16W | 0402 | Yageo | RC0402FR-075K1L | LCSC | C105872
27 | 2 | R3, R4 | RES SMD 0 OHM 1% 1/16W | 0402 | Yageo | RC0402FR-070RL | LCSC | C106231
28 | 1 | R5 | RES SMD 24K OHM 1% 1/16W | 0402 | Yageo | RC0402FR-0724KL | LCSC | C138026
29 | 1 | R6 | RES SMD 47K OHM 1% 1/16W | 0402 | Yageo | RC0402FR-0747KL | LCSC | C93943
30 | 6 | R7, R8, R9, R10, R15, R16 | RES SMD 12K OHM 1% 1/16W | 0402 | Yageo | RC0402FR-0712KL | LCSC | C114760
31 | 2 | R11, R12 | RES SMD 2.2K OHM 1% 1/16W | 0402 | Yageo | RC0402FR-072K2L | LCSC | C114762
32 | 3 | R13, R14, R17 | RES SMD 100K OHM 1% 1/16W | 0402 | Yageo | RC0402FR-07100KL | LCSC | C60491
33 | 1 | U1 | Module WIFI | 38-SMD | Espressif | ESP32-WROOM-32 | LCSC | C95209
34 | 1 | U2 | Transceiver USB 1/1 2Mbps | QFN-24 | SILICON LABS | CP2104-F03-GMR | LCSC | C47742
35 | 1 | U3 | Fixed 15V 3.3V 800mA | SOT-223 | Texas | LM1117MPX-3.3/NOPB | LCSC | C9662
36 | 1 | U4 | Fixed 15V 5V 800mA | SOT-223 | Texas | LM1117MPX-5.0/NOPB | LCSC | C9663
37 | 1 | U5 | Unidirectional 3V 6.1V | SOT-323-5 | STMicro | ESDA6V1W5 | LCSC | C48677
38 | 1 | USB1 | USB - Type C Receptacle | 24-SMD | MOLEX | 105450-0101 | LCSC | C134092
39 | 1 | USB2 | NC - USB - Type B Receptacle USB 2 4 | 4-PTH | MOLEX | 67068-8000 | LCSC | C114097 | Not installed

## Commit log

2020-02-09 :neckbeard: Added .gitattributes & .gitignore files
2020-02-09 20191212
2020-02-10 20191214

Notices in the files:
parts and their libraries:
SparkFun-Connectors: Licensing: Creative Commons ShareAlike 4.0 International - https://creativecommons.org/licenses/by-sa/4.0
switch-alps: Copyright (C) 2009, Bob Starr
cap-pan40: Copyright (C) 2004, Bob Starr
